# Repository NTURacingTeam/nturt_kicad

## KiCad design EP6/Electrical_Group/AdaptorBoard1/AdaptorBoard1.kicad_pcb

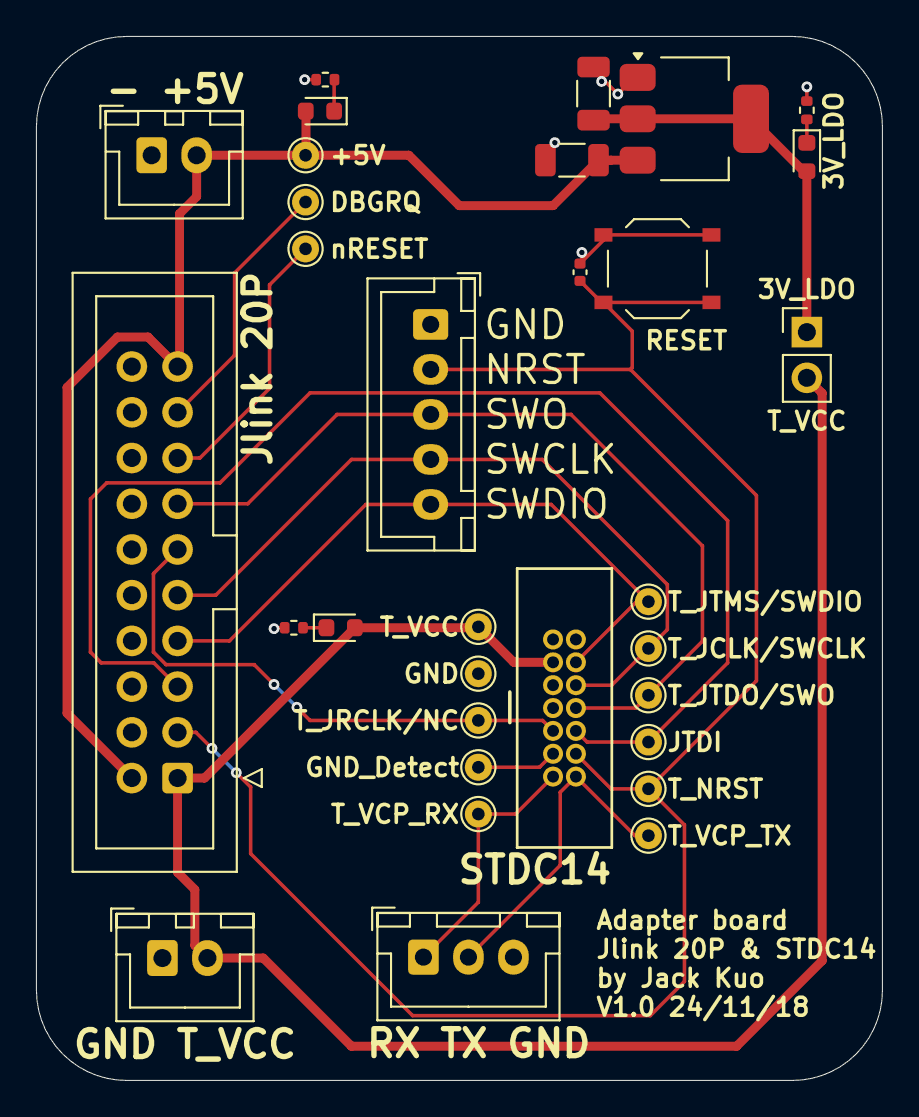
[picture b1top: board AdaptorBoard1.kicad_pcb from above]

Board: 2 copper layers, 47.0 x 58.0 mm, 32 parts (0 on the bottom side), 18 nets.

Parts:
C1, C2: 47u 10V; C_1206_3216Metric
C3: 0u1; C_0402_1005Metric
D1: RED 3V3; LED_0603_1608Metric
D2: RED 5V; LED_0603_1608Metric
D3: RED T_VCC; LED_0603_1608Metric
J1: Jlink20p; IDC-Header_2x10_P2.54mm_Vertical
J2: SWD; JST_XH_B5B-XH-A_1x05_P2.50mm_Vertical
J11: T_VCC; JST_XH_B2B-XH-A_1x02_P2.50mm_Vertical
J12: VCP_UART; JST_XH_B3B-XH-A_1x03_P2.50mm_Vertical
J13: 5V; JST_XH_B2B-XH-A_1x02_P2.50mm_Vertical
J17: STDIC 14p; box_header_14P_pitch127
JP1: 3.3V T_VCC; PinHeader_1x02_P2.54mm_Vertical
R1, R2, R3: 1k; R_0402_1005Metric
SW1: TS-1187A-B-A-B; SW_Push_1P1T_XKB_TS-1187A
TP1, TP2: T_VCC; TestPoint_THTPad_D1.5mm_Drill0.7mm
TP3: T_JRCLK/NC; TestPoint_THTPad_D1.5mm_Drill0.7mm
TP4: GND_DETECT; TestPoint_THTPad_D1.5mm_Drill0.7mm
TP5: T_VCP_RX; TestPoint_THTPad_D1.5mm_Drill0.7mm
TP8: T_JTMS/SWDIO; TestPoint_THTPad_D1.5mm_Drill0.7mm
TP9: T_JCLK/SWCLK; TestPoint_THTPad_D1.5mm_Drill0.7mm
TP10: T_JTDO/SWO; TestPoint_THTPad_D1.5mm_Drill0.7mm
TP11: T_NRST; TestPoint_THTPad_D1.5mm_Drill0.7mm
TP12: T_JTDI/NC; TestPoint_THTPad_D1.5mm_Drill0.7mm
TP13: T_VCP_TX; TestPoint_THTPad_D1.5mm_Drill0.7mm
TP14: nRESET; TestPoint_THTPad_D1.5mm_Drill0.7mm
TP15: DBGRQ; TestPoint_THTPad_D1.5mm_Drill0.7mm
TP16: +5V; TestPoint_THTPad_D1.5mm_Drill0.7mm
U1: AMS1117-3.3; SOT-223-3_TabPin2

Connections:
/STDIC14_JLINK20p/3V_LDO: C2.1, D1.2 (A), JP1.1 (A), U1.2 (VO)
/STDIC14_JLINK20p/+5V: C1.1, D2.2 (A), J1.2, J1.19, J13.2, TP16.1, U1.3 (VI)
/STDIC14_JLINK20p/DBGRQ: J1.17, TP15.1
/STDIC14_JLINK20p/GND_Detect: J17.11 (GNDDetect), TP4.1
/STDIC14_JLINK20p/T_JCLK/SWCLK: J1.9, J2.4, J17.6 (JCLK/SWCLK), TP9.1
/STDIC14_JLINK20p/T_JRCLK/NC: J1.11, J17.9 (JRCLK/NC), TP3.1
/STDIC14_JLINK20p/T_JTDI/NC: J1.5, J17.10 (JTDI/NC), TP12.1
/STDIC14_JLINK20p/T_JTDO/SWO: J1.13, J2.3, J17.8 (JTDO/SWO), TP10.1
/STDIC14_JLINK20p/T_JTMS/SWDIO: J1.7, J2.5, J17.4 (JTMS/SWDIO), TP8.1
/STDIC14_JLINK20p/T_NRST: C3.1, J1.3, J2.2, J17.12 (~RST), SW1.2, TP11.1
/STDIC14_JLINK20p/T_VCC: D3.2 (A), J1.1, J11.2, J17.3 (VCC), JP1.2 (B), TP1.1
/STDIC14_JLINK20p/T_VCP_RX: J12.1, J17.13 (VCP_RX), TP5.1
/STDIC14_JLINK20p/T_VCP_TX: J12.2, J17.14 (VCP_TX), TP13.1
/STDIC14_JLINK20p/nRESET: J1.15, TP14.1
GND: C1.2, C2.2, C3.2, J1.4, J1.6, J1.8, J1.10, J1.12, J1.14, J1.16, J1.18, J1.20, J2.1, J11.1, J12.3, J13.1, J17.5 (GND), J17.7 (GND), R1.2, R2.2, R3.2, SW1.1, TP2.1, U1.1 (GND)
unnamed: D1.1 (K), R1.1
unnamed: D2.1 (K), R2.1
unnamed: D3.1 (K), R3.1

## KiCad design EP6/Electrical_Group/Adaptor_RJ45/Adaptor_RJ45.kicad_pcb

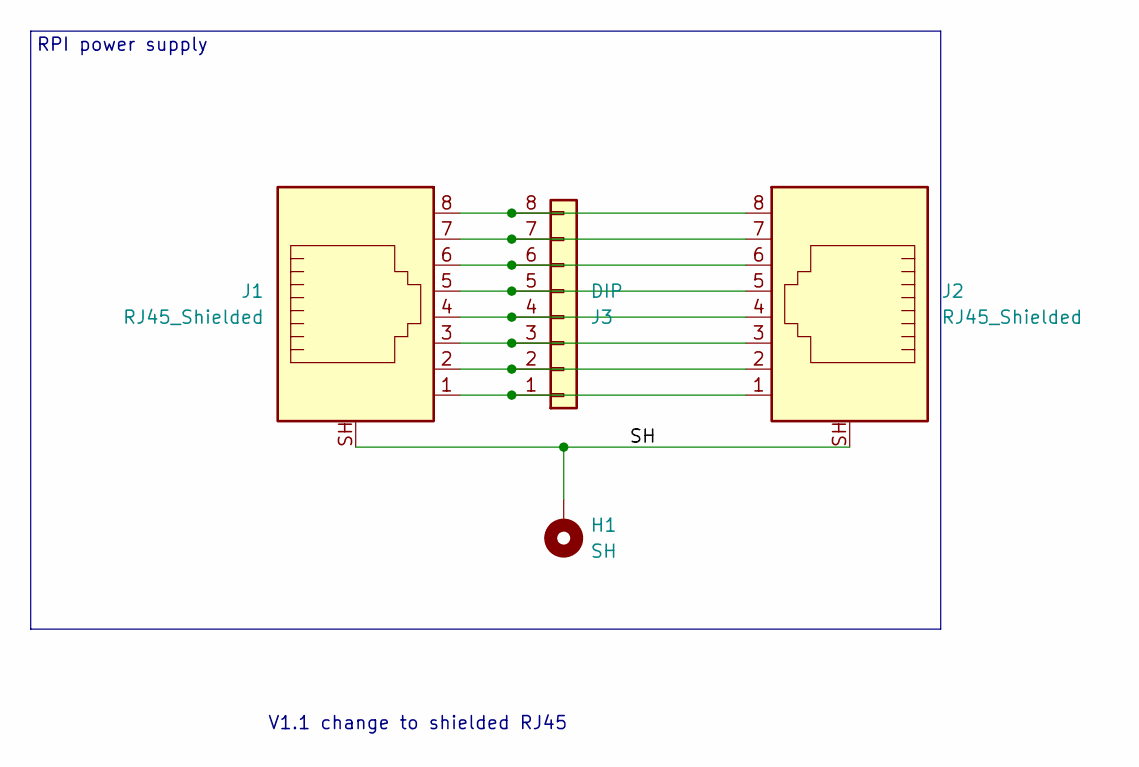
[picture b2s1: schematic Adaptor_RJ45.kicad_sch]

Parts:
H1: SH; MountingHole_3.2mm_M3_Pad
J1, J2: RJ45_Shielded; RJ45_Ninigi_GE
J3: DIP; PinHeader_2x04_P2.54mm_Vertical

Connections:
/SH: H1.1, J1.SH, J2.SH
unnamed: J1.1, J2.1, J3.1
unnamed: J1.2, J2.2, J3.2
unnamed: J1.3, J2.3, J3.3
unnamed: J1.4, J2.4, J3.4
unnamed: J1.5, J2.5, J3.5
unnamed: J1.6, J2.6, J3.6
unnamed: J1.7, J2.7, J3.7
unnamed: J1.8, J2.8, J3.8

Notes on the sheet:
RPI power supply
V1.1 change to shielded RJ45

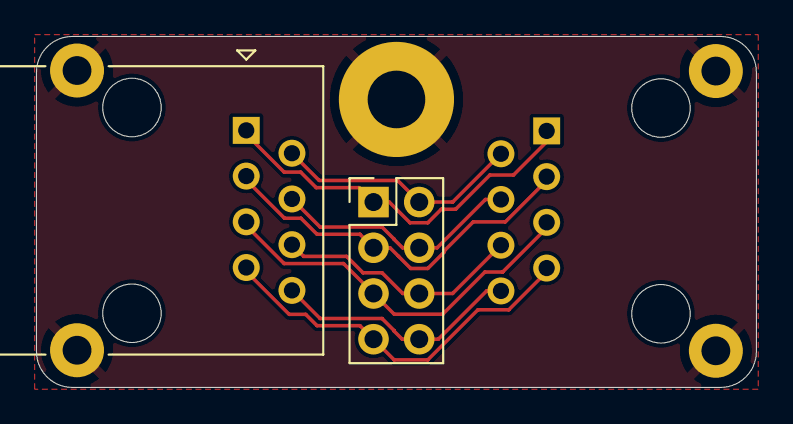
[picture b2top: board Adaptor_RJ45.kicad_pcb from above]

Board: 2 copper layers, 40.0 x 19.5 mm, 4 parts (1 on the bottom side), 9 nets.

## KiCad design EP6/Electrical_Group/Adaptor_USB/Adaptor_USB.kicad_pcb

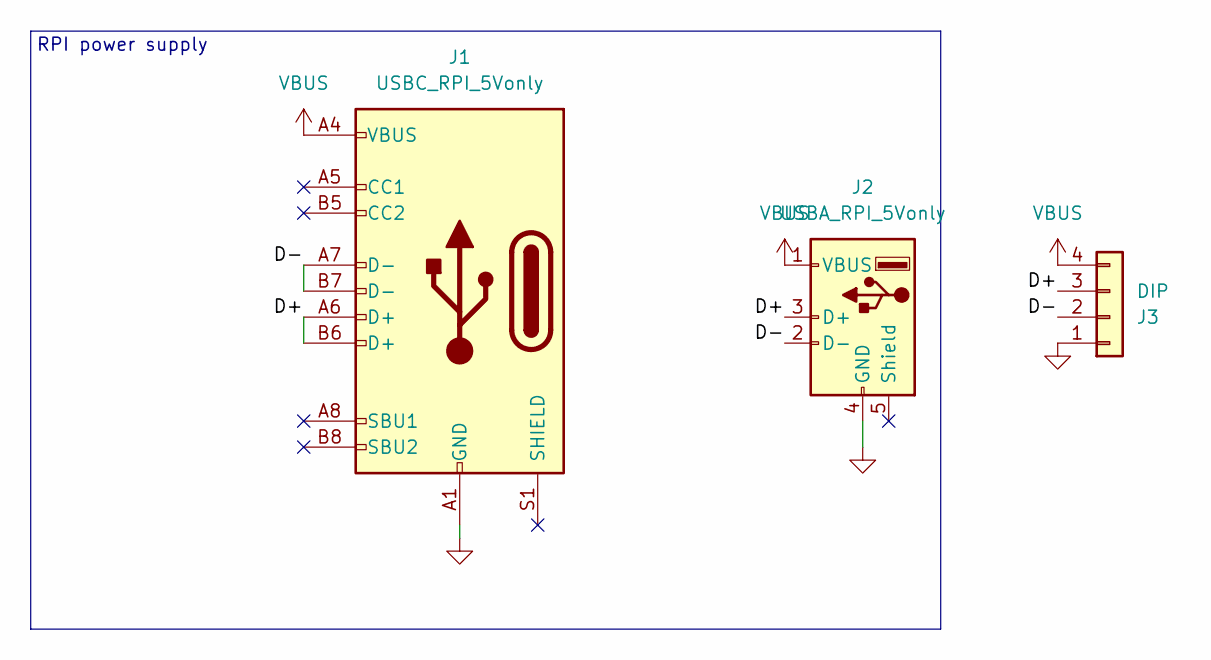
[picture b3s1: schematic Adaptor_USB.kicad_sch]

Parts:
J1: USBC_RPI_5Vonly; USB_C_Receptacle_GCT_USB4105-xx-A_16P_TopMnt_Horizontal
J2: USBA_RPI_5Vonly; USB_A_Molex_67643_Horizontal
J3: DIP; PinHeader_1x04_P2.54mm_Vertical; Part Number 1-0401FBV0T

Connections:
/D+: J1.A6 (D+), J1.B6 (D+), J2.3 (D+), J3.3
/D-: J1.A7 (D-), J1.B7 (D-), J2.2 (D-), J3.2
GND: J1.A1 (GND), J1.A12 (GND), J1.B1 (GND), J1.B12 (GND), J2.4 (GND), J3.1
VBUS: J1.A4 (VBUS), J1.A9 (VBUS), J1.B4 (VBUS), J1.B9 (VBUS), J2.1 (VBUS), J3.4

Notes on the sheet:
RPI power supply

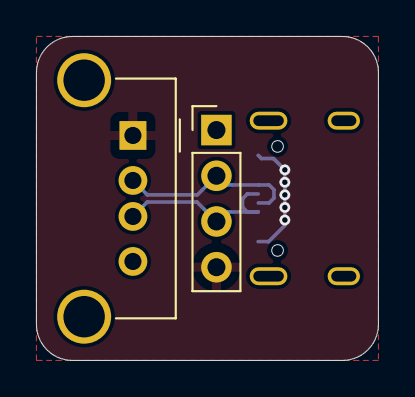
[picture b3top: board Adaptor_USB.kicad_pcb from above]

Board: 2 copper layers, 19.0 x 18.0 mm, 3 parts (1 on the bottom side), 4 nets.

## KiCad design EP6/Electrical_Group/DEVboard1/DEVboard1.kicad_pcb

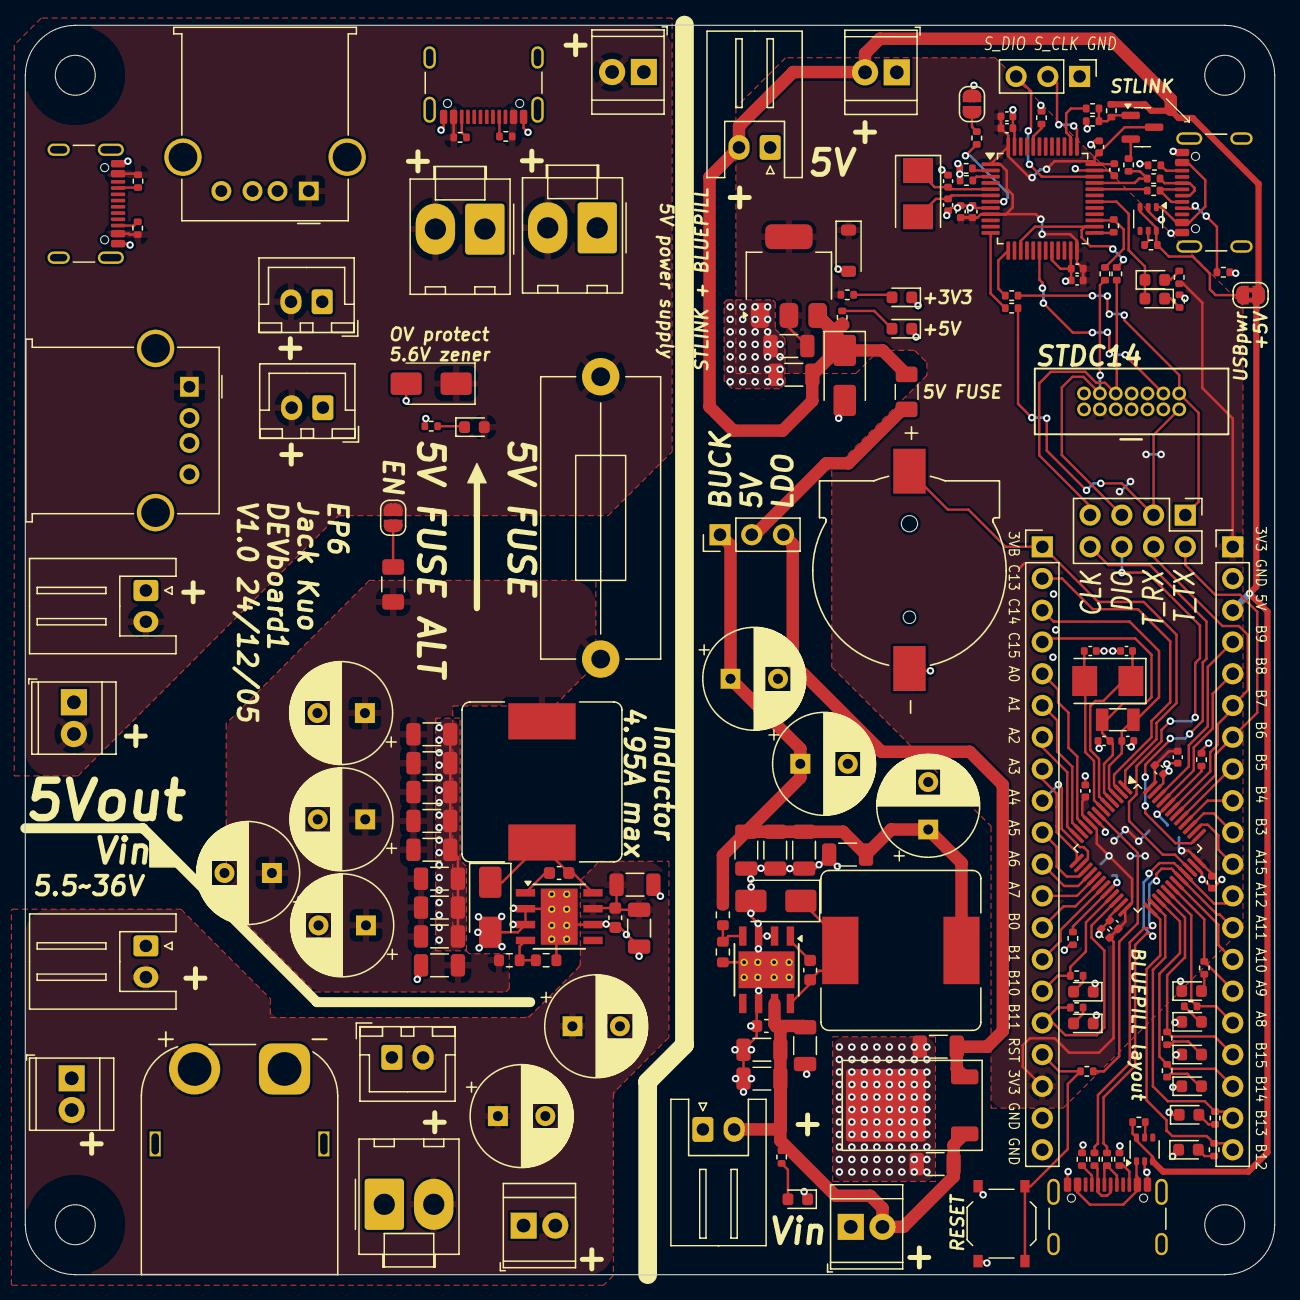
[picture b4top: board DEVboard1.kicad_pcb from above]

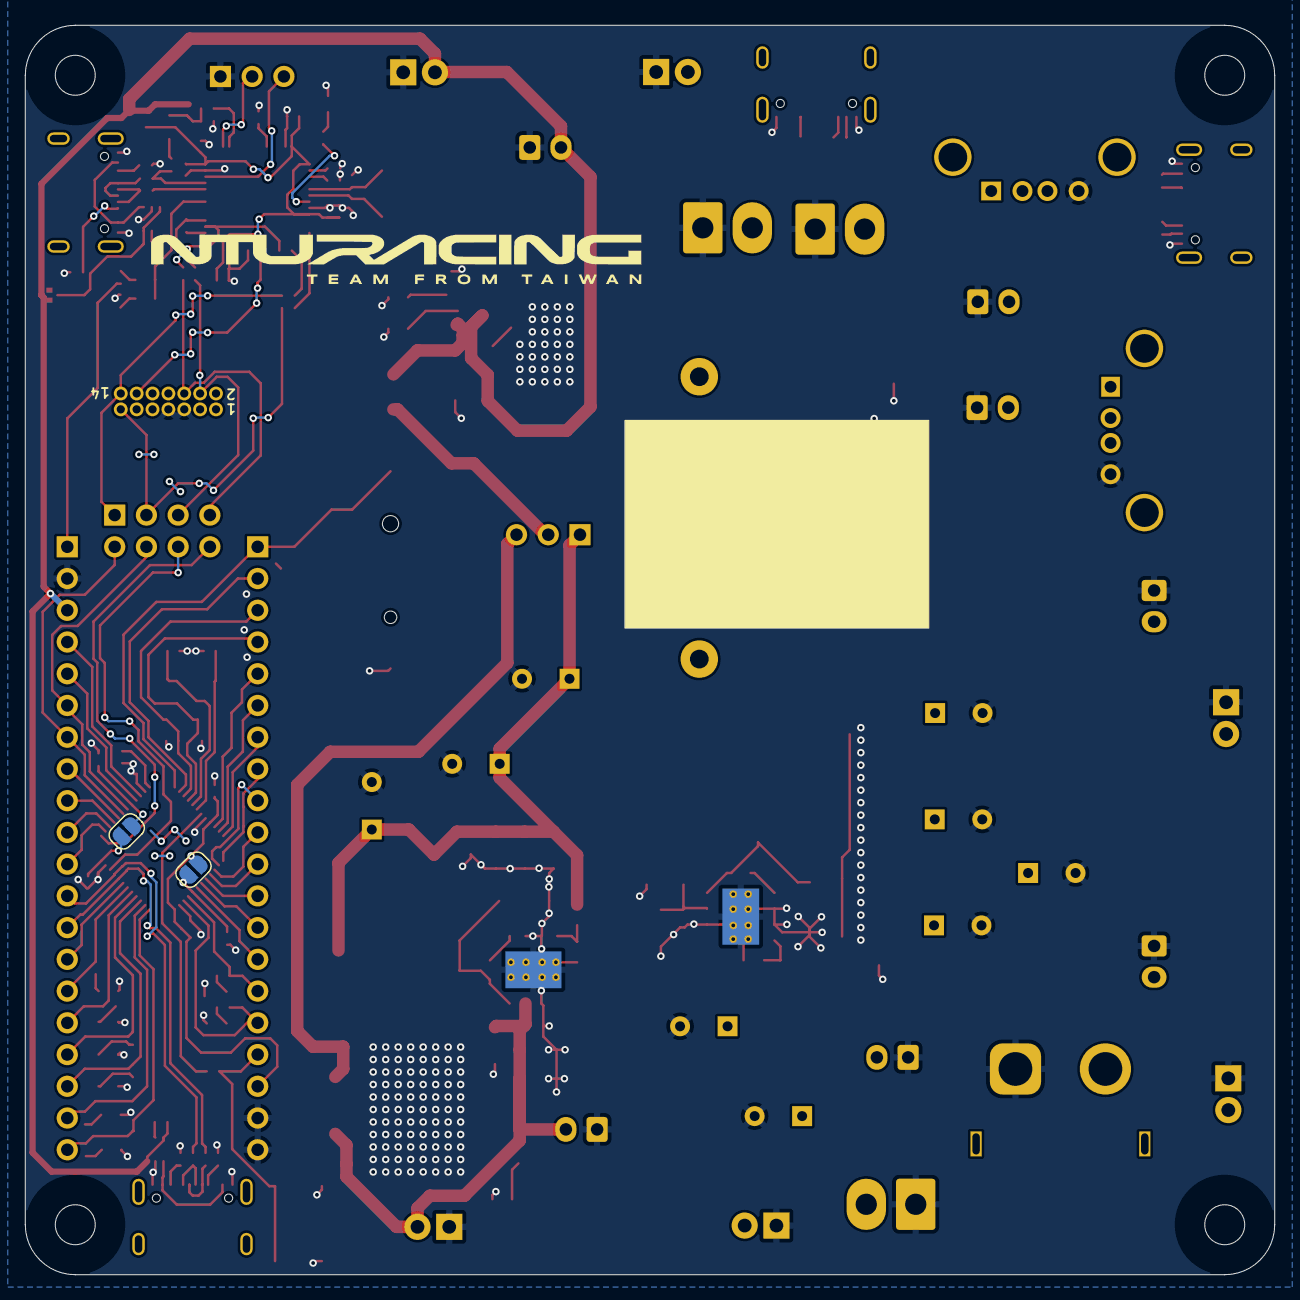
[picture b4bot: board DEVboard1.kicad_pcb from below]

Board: 2 copper layers, 100.0 x 100.0 mm, 179 parts (2 on the bottom side), 114 nets.

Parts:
BT1: 1056; BAT_1056
C1, C2, C3, C4, C13, C14: 10u 6V; C_0402_1005Metric
C5, C6, C7, C8, C15, C16, C17, C18: 0u1; C_0402_1005Metric
C9, C10: 33p; C_0402_1005Metric
C11, C12: 15p; C_0402_1005Metric
C19, C20: 30p; C_0402_1005Metric
C21, C22: 47u 10V; C_1206_3216Metric
C23, C33: 10n; C_0603_1608Metric
C24, C25, C31, C32, C34, C35, C45: 10u 35V; C_1206_3216Metric
C26, C37: 0u1; C_0603_1608Metric
C27, C28, C29, C30, C38, C39, C40, C41, C42, C46, C47, C48, C49: 22u 25V; C_1206_3216Metric
C36, C43, C44, C50, C51, C52, C53, C54, C55: 330u 25V; CP_Radial_D8.0mm_P3.80mm
D1: YELLOW led; LED_0603_1608Metric
D2: 3.3V 123 (BZT52B3V3); D_SOD-123
D3, D17, D19, D20: RED LED; LED_0603_1608Metric
D4: RED led; LED_0603_1608Metric
D5, D18: 5.6V 1SMA5919A; D_SMA
D6, D7, D9, D10, D11, D12, D13, D14: WHITE LED; LED_0603_1608Metric
D8, D15: SS54; D_SMA
F1: 0.5A; Fuse_1206_3216Metric
F2: 5Vbuck_fuse; Fuseholder_Cylinder-5x20mm_Stelvio-Kontek_PTF78_Horizontal_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
F3: 5Vbuck_PPTC; Fuse_1206_3216Metric
H1, H2, H3, H4: MountingHole; MountingHole_3.2mm_M3
J1, J4: USB_C_stm32; USB_C_Receptacle_GCT_USB4105-xx-A_16P_TopMnt_Horizontal
J2, J3: Conn_01x20; PinHeader_1x20_P2.54mm_Vertical
J5: STDC14; box_header_14P_pitch127
J6: DEBUG; PinHeader_2x04_P2.54mm_Vertical
J7: S_SWD; PinHeader_1x03_P2.54mm_Vertical
J8: 5V_source; PinHeader_1x03_P2.54mm_Vertical
J9, J11, J29: +5V; JST_XH_S2B-XH-A_1x02_P2.50mm_Horizontal
J10: +5V; TerminalBlock_TE_282834-2_1x02_P2.54mm_Horizontal
J12, J27: Vin; TerminalBlock_TE_282834-2_1x02_P2.54mm_Horizontal
J13: Vin; Molex_KK-396_A-41791-0002_1x02_P3.96mm_Vertical
J14: Vin; JST_XH_B2B-XH-A_1x02_P2.50mm_Vertical
J15: Vin; AMASS_XT60PW-M_1x02_P7.20mm_Horizontal
J16, J25, J26: +24V; TerminalBlock_TE_282834-2_1x02_P2.54mm_Horizontal
J17, J18: +5V; Molex_KK-396_A-41791-0002_1x02_P3.96mm_Vertical
J19, J22: USBC_RPI_5Vonly; USB_C_Receptacle_GCT_USB4105-xx-A_16P_TopMnt_Horizontal
J20, J23: USBA_RPI_5Vonly; USB_A_Molex_67643_Horizontal
J21, J24: +5V; JST_XH_B2B-XH-A_1x02_P2.50mm_Vertical
J30: Vin; JST_XH_S2B-XH-A_1x02_P2.50mm_Horizontal
JP1: BOOT0; SolderJumper-2_P1.3mm_Open_RoundedPad1.0x1.5mm
JP2: BOOT1; SolderJumper-2_P1.3mm_Open_RoundedPad1.0x1.5mm
JP3: S_RESET; SolderJumper-2_P1.3mm_Open_RoundedPad1.0x1.5mm
JP4: VBUS_5V; SolderJumper-2_P1.3mm_Bridged2Bar_RoundedPad1.0x1.5mm
JP5: PPTC_EN; SolderJumper-2_P1.3mm_Open_RoundedPad1.0x1.5mm
L1, L2: 22uH 3.7A (SMDRI129-220MT); L_Bourns_SRR1260
Q1: MMBT3904; SOT-23
R1, R4, R7, R8, R19, R21, R27, R28: 100R; R_0402_1005Metric
R2, R5, R10: 100k; R_0402_1005Metric
R3, R6, R11, R13, R18, R20, R26: 10k; R_0402_1005Metric
R9, R15: 220R; R_0402_1005Metric
R12, R14: 10R; R_0402_1005Metric
R16, R17, R23, R24: 5k1; R_0402_1005Metric
R22: 33k; R_0402_1005Metric
R25: 1k5; R_0402_1005Metric
R31, R32, R33, R35, R36, R37, R38, R39, R40, R43, R46, R48: 1k; R_0402_1005Metric
R34, R41: 47k 1%; R_0603_1608Metric
R42, R44: 15k 1%; R_0603_1608Metric
R45, R47, R49, R50: 56k; R_0402_1005Metric
SW1: TS-1187A-B-A-B; SW_Push_1P1T_XKB_TS-1187A
U1, U2: STM32F103CBT6; LQFP-48_7x7mm_P0.5mm
U3, U5: LM66100DCK; SOT-363_SC-70-6
U4: AMS1117-3.3; SOT-223-3_TabPin2
U6: L78M05ABDT; TO-252-2
U7, U8: TPS5430DDAR; TI_SO-PowerPAD-8_ThermalVias
Y1, Y3: 8MHz X50328MSB2GI; Crystal_SMD_5032-2Pin_5.0x3.2mm
Y2: 32.768kHz Q13FC13500004; Crystal_SMD_3215-2Pin_3.2x1.5mm

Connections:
+3V3: C1.1, C2.1, C3.1, C4.1, C5.1, C6.1, C7.1, C8.1, C13.1, C14.1, C15.1, C16.1, C17.1, C18.1, C22.1, D2.1 (K), J2.18, J3.1, J5.3, JP1.2 (B), JP2.2 (B), Q1.3 (C), R9.1, R46.1, U1.9 (VDDA), U1.24 (VDD), U1.36 (VDD), U1.48 (VDD), U2.1 (VBAT), U2.9 (VDDA), U2.24 (VDD), U2.36 (VDD), U2.48 (VDD), U4.2 (VO)
+5V: C21.1, D5.1 (K), F1.2, J3.3, J11.2, J26.2, JP4.2 (B), R20.1, R26.1, R48.1, U4.3 (VI), U5.3 (~CE), U5.6 (VOUT)
/5V_buck_FB: R34.2, R42.1, U7.4 (VSENSE)
/5V_buck_sw: C23.2, D8.1 (K), L1.1, U7.8 (PH)
/+5V_LDO: C32.2, J8.3, U6.3 (OUT)
/+5V_buck: C27.1, C28.1, C29.1, C30.1, C36.1, C54.1, C55.1, J8.1, L1.2, R34.1
/MCU/3VB: BT1.P, J2.1, U1.1 (VBAT)
/MCU/BOOT0: JP1.1 (A), R5.1, U1.44 (BOOT0)
/MCU/BOOT1: JP2.1 (A), R2.1, U1.20 (PB2)
/MCU/NRST: R3.2, U1.7 (NRST)
/MCU/OSC32_IN: C11.1, J2.3, U1.3 (PC14), Y2.1
/MCU/OSC32_OUT: C12.1, J2.4, U1.4 (PC15), Y2.2
/MCU/OSC_IN: C9.1, U1.5 (PD0), Y1.1
/MCU/OSC_OUT: C10.1, U1.6 (PD1), Y1.2
/MCU/PA0: J2.5, U1.10 (PA0)
/MCU/PA1: J2.6, U1.11 (PA1)
/MCU/PA2: J2.7, U1.12 (PA2)
/MCU/PA3: J2.8, U1.13 (PA3)
/MCU/PA4: J2.9, U1.14 (PA4)
/MCU/PA5: J2.10, U1.15 (PA5)
/MCU/PA6: J2.11, U1.16 (PA6)
/MCU/PA7: J2.12, U1.17 (PA7)
/MCU/PA8: J3.16, R36.1, U1.29 (PA8)
/MCU/PA9: J3.15, R35.1, U1.30 (PA9)
/MCU/PA10: J3.14, U1.31 (PA10)
/MCU/PA13: J6.6, U1.34 (PA13)
/MCU/PA14: J6.8, U1.37 (PA14)
/MCU/PA15: J3.11, U1.38 (PA15)
/MCU/PB0: J2.13, U1.18 (PB0)
/MCU/PB1: J2.14, U1.19 (PB1)
/MCU/PB3: J3.10, U1.39 (PB3)
/MCU/PB4: J3.9, U1.40 (PB4)
/MCU/PB5: J3.8, U1.41 (PB5)
/MCU/PB6: J3.7, J6.2, U1.42 (PB6)
/MCU/PB7: J3.6, J6.4, U1.43 (PB7)
/MCU/PB8: J3.5, U1.45 (PB8)
/MCU/PB9: J3.4, U1.46 (PB9)
/MCU/PB10: J2.15, R32.1, U1.21 (PB10)
/MCU/PB11: J2.16, R33.1, U1.22 (PB11)
/MCU/PB12: J3.20, R40.1, U1.25 (PB12)
/MCU/PB13: J3.19, R39.1, U1.26 (PB13)
/MCU/PB14: J3.18, R38.1, U1.27 (PB14)
/MCU/PB15: J3.17, R37.1, U1.28 (PB15)
/MCU/PC13: J2.2, U1.2 (PC13)
/MCU/RESET: J2.17, R3.1, SW1.2
/MCU/USB_D+: J1.A6 (D+), J1.B6 (D+), R14.2
/MCU/USB_D-: J1.A7 (D-), J1.B7 (D-), R12.2
/MCU/USB_DN: J3.13, R12.1, U1.32 (PA11)
/MCU/USB_DP: J3.12, R14.1, U1.33 (PA12)
/MCU/VBUS: J1.A4 (VBUS), J1.A9 (VBUS), J1.B4 (VBUS), J1.B9 (VBUS), U5.1 (VIN)
/STlink/BOOT0: R10.1, U2.44 (BOOT0)
/STlink/LED_STLINK: D1.1 (K), D4.2 (A), U2.30 (PA9)
/STlink/OSC_IN: C19.1, U2.5 (PD0), Y3.1
/STlink/OSC_OUT: C20.1, U2.6 (PD1), Y3.2
/STlink/RENUM: R21.1, U2.38 (PA15)
/STlink/S_CLK: J7.2, U2.37 (PA14)
/STlink/S_DIO: J7.3, U2.34 (PA13)
/STlink/S_NRST: R6.2, U2.7 (NRST)
/STlink/USART2_RX: R4.1, U2.13 (PA3)
/STlink/USART2_TX: R1.1, U2.12 (PA2)
/STlink/USB_D+: J4.A6 (D+), J4.B6 (D+), R28.1
/STlink/USB_D-: J4.A7 (D-), J4.B7 (D-), R27.1
/STlink/USB_DN: R27.2, U2.32 (PA11)
/STlink/USB_DP: R25.2, R28.2, U2.33 (PA12)
/STlink/VBUS: J4.A4 (VBUS), J4.A9 (VBUS), J4.B4 (VBUS), J4.B9 (VBUS), U3.1 (VIN)
/STlink/t_CLK: R7.1, U2.15 (PA5), U2.26 (PB13)
/STlink/t_DIO: R8.1, R19.1, U2.27 (PB14)
/T_NRST: J5.12, U2.18 (PB0)
/T_SWCLK: J5.6, J6.7, R7.2
/T_SWDIO: J5.4, J6.5, R8.2
/T_VCP_RX: J5.13, J6.3, R1.2
/T_VCP_TX: J5.14, J6.1, R4.2
/extPWR/5V_buck_FB: R41.2, R44.1, U8.4 (VSENSE)
/extPWR/5V_buck_sw: C33.2, D15.1 (K), L2.1, U8.8 (PH)
/extPWR/+5V_buck: D17.2 (A), D18.1 (K), F2.2, J10.2, J17.2, J18.2, J19.A4 (VBUS), J19.A9 (VBUS), J19.B4 (VBUS), J19.B9 (VBUS), J20.1 (VBUS), J21.2, J22.A4 (VBUS), J22.A9 (VBUS), J22.B4 (VBUS), J22.B9 (VBUS), J23.1 (VBUS), J24.2, J25.2, J29.2, JP5.2 (B), R45.1, R47.1, R49.1, R50.1
/extPWR/+5V_buck_raw: C38.1, C39.1, C40.1, C41.1, C42.1, C43.1, C44.1, C46.1, C47.1, C48.1, C49.1, C50.1, C51.1, F2.1, F3.1, L2.2, R41.1
/extPWR/Vin: C34.1, C35.1, C37.2, C52.1, C53.1, J12.2, J13.2, J14.2, J15.2, J27.2, J30.2, U8.7 (VIN)
GND: BT1.N, C1.2, C2.2, C3.2, C4.2, C5.2, C6.2, C7.2, C8.2, C9.2, C10.2, C11.2, C12.2, C13.2, C14.2, C15.2, C16.2, C17.2, C18.2, C19.2, C20.2, C21.2, C22.2, C24.2, C25.2, C26.1, C27.2, C28.2, C29.2, C30.2, C31.2, C32.1, C34.2, C35.2, C36.2, C37.1, C38.2, C39.2, C40.2, C41.2, C42.2, C43.2, C44.2, C45.2, C46.2, C47.2, C48.2, C49.2, C50.2, C51.2, C52.2, C53.2, C54.2, C55.2, D2.2 (A), D3.1 (K), D5.2 (A), D6.1 (K), D7.1 (K), D8.2 (A), D9.1 (K), D10.1 (K), D11.1 (K), D12.1 (K), D13.1 (K), D14.1 (K), D15.2 (A), D18.2 (A), D19.1 (K), D20.1 (K), J1.A1 (GND), J1.A12 (GND), J1.B1 (GND), J1.B12 (GND), J2.19, J2.20, J3.2, J4.A1 (GND), J4.A12 (GND), J4.B1 (GND), J4.B12 (GND), J5.5, J5.7, J7.1, J9.1, J10.1, J11.1, J12.1, J13.1, J14.1, J15.1, J16.1, J17.1, J18.1, J19.A1 (GND), J19.A12 (GND), J19.B1 (GND), J19.B12 (GND), J20.4 (GND), J21.1, J22.A1 (GND), J22.A12 (GND), J22.B1 (GND), J22.B12 (GND), J23.4 (GND), J24.1, J25.1, J26.1, J27.1, J29.1, J30.1, JP3.1 (A), R2.2, R5.2, R10.2, R11.2, R13.2, R15.2, R16.1, R17.1, R22.2, R23.1, R24.1, R42.2, R43.2, R44.2, SW1.1, U1.8 (VSSA), U1.23 (VSS), U1.35 (VSS), U1.47 (VSS), U2.8 (VSSA), U2.20 (PB2), U2.23 (VSS), U2.35 (VSS), U2.47 (VSS), U3.2 (GND), U4.1 (GND), U5.2 (GND), U6.2, U7.2 (NC), U7.3 (NC), U7.6 (GND), U7.9 (GNDPAD), U8.2 (NC), U8.3 (NC), U8.6 (GND), U8.9 (GNDPAD)
unnamed: D1.2 (A), R9.2
unnamed: D3.2 (A), R31.2
unnamed: D4.1 (K), R15.1
unnamed: D6.2 (A), R32.2
unnamed: D7.2 (A), R33.2
unnamed: D9.2 (A), R35.2
unnamed: D10.2 (A), R36.2
unnamed: D11.2 (A), R37.2
unnamed: D12.2 (A), R38.2
unnamed: D13.2 (A), R39.2
unnamed: D14.2 (A), R40.2
unnamed: D17.1 (K), R43.1
unnamed: D19.2 (A), R48.2
unnamed: D20.2 (A), R46.2
unnamed: J1.A5 (CC1), R16.2
unnamed: J1.B5 (CC2), R17.2
unnamed: J4.A5 (CC1), R23.2
unnamed: J4.B5 (CC2), R24.2
unnamed: F1.1, J8.2
unnamed: J19.A5 (CC1), R45.2
unnamed: J19.B5 (CC2), R47.2
unnamed: J22.A5 (CC1), R49.2
unnamed: J22.B5 (CC2), R50.2
unnamed: JP3.2 (B), R6.1
unnamed: JP4.1 (A), R18.1, U3.3 (~CE), U3.6 (VOUT)
unnamed: F3.2, JP5.1 (A)
unnamed: Q1.1 (B), R20.2, R21.2, R22.1
unnamed: Q1.2 (E), R25.1
unnamed: R19.2, U2.25 (PB12)
unnamed: R11.1, U2.2 (PC13)
unnamed: R13.1, U2.3 (PC14)
unnamed: R18.2, U3.5 (ST)
unnamed: R26.2, U5.5 (ST)
unnamed: C23.1, U7.1 (BOOT)
unnamed: C33.1, U8.1 (BOOT)
VBUS: C24.1, C25.1, C26.2, C31.1, C45.1, J9.2, J16.2, R31.1, U6.1 (IN), U7.7 (VIN)

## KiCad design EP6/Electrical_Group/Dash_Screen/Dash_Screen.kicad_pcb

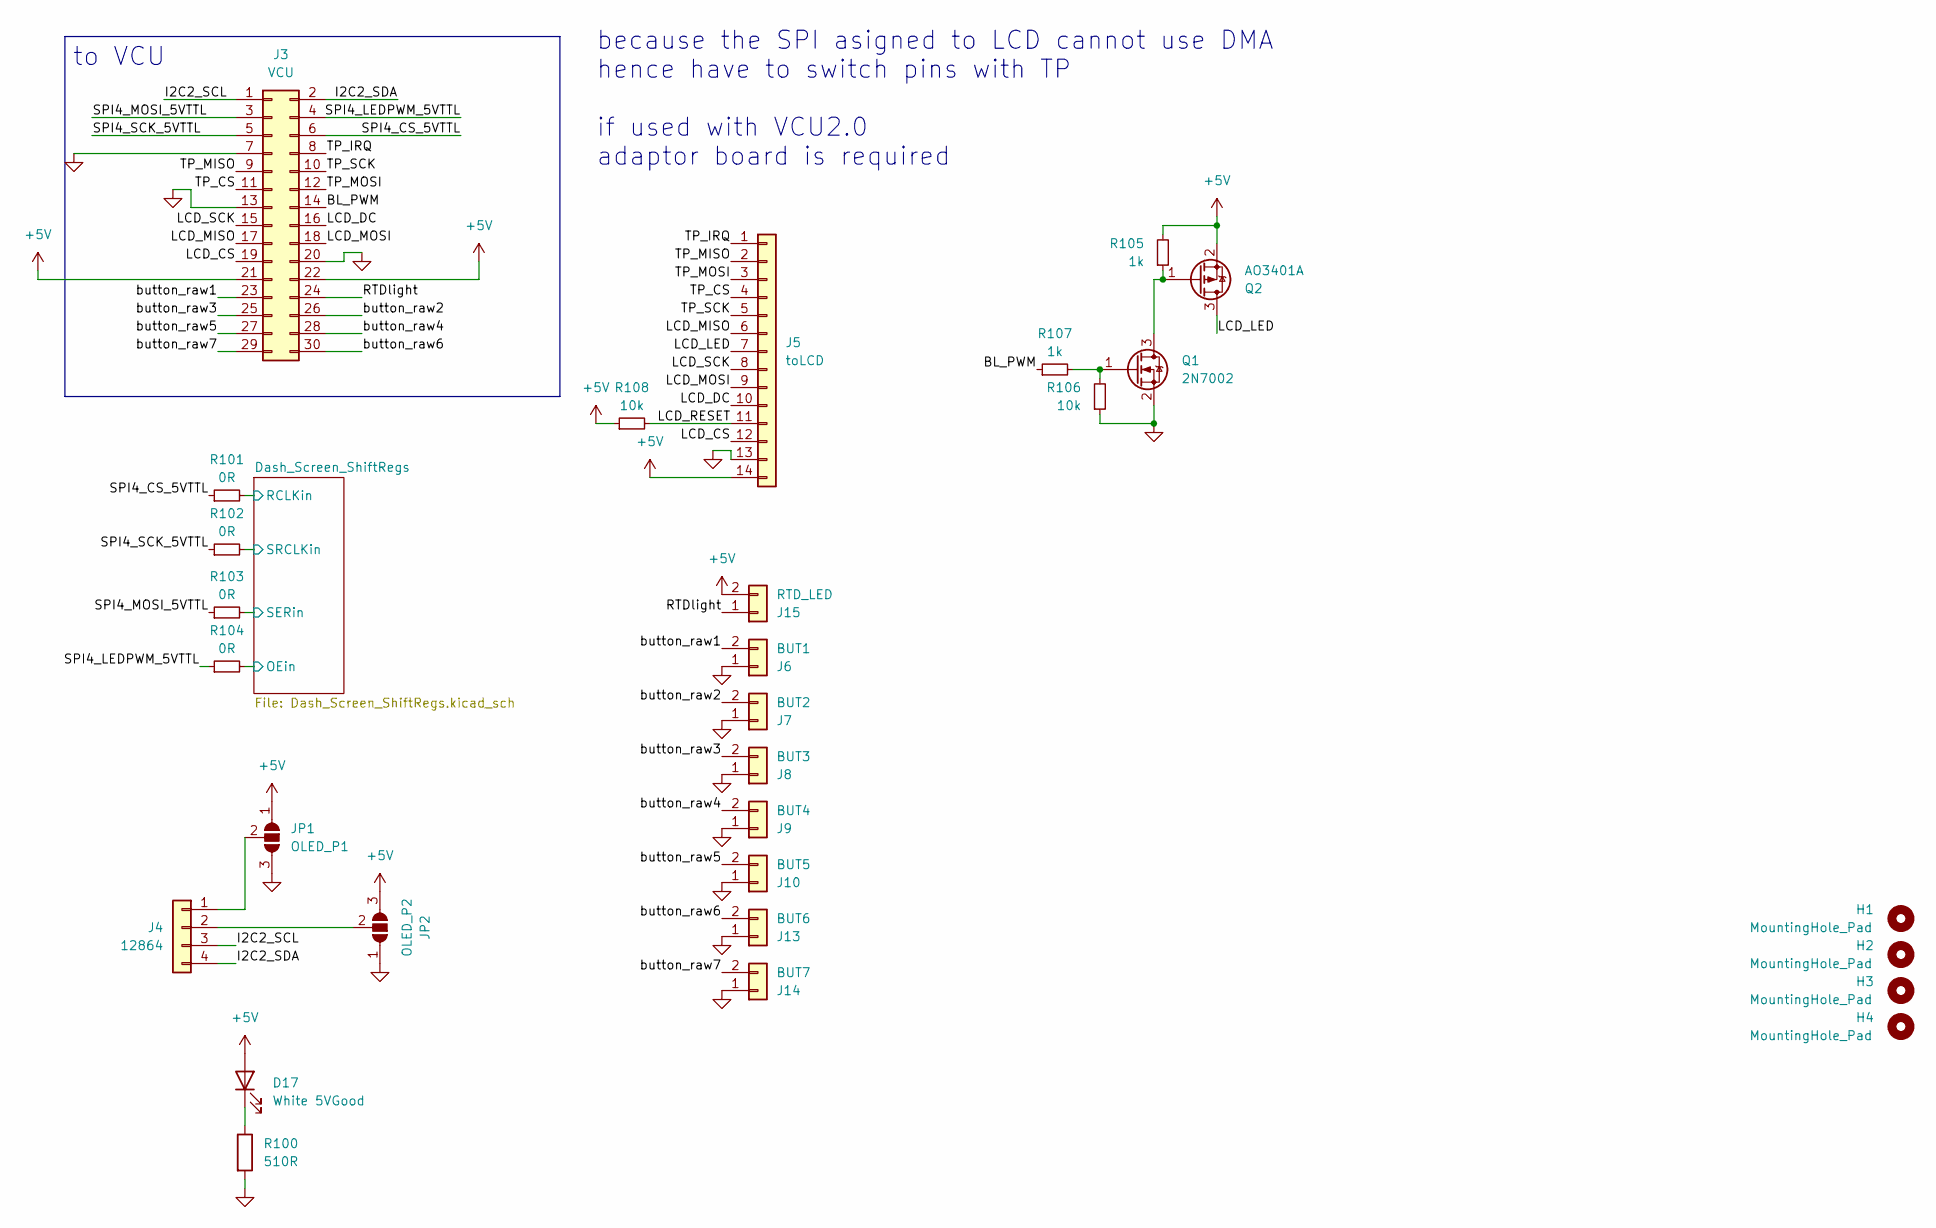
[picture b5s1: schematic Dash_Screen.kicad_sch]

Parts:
D17: White 5VGood; LED_0603_1608Metric
H1, H2, H3, H4: MountingHole_Pad; MountingHole_3.2mm_M3
J3: VCU; IDC-Header_2x15_P2.54mm_Vertical_SMD
J4: 12864; 12864_1.3_I2C
J5: toLCD; PinHeader_1x14_P2.54mm_Horizontal
J6: BUT1; JST_PH_S2B-PH-K_1x02_P2.00mm_Horizontal
J7: BUT2; JST_PH_S2B-PH-K_1x02_P2.00mm_Horizontal
J8: BUT3; JST_PH_S2B-PH-K_1x02_P2.00mm_Horizontal
J9: BUT4; JST_PH_S2B-PH-K_1x02_P2.00mm_Horizontal
J10: BUT5; JST_PH_S2B-PH-K_1x02_P2.00mm_Horizontal
J13: BUT6; JST_PH_S2B-PH-K_1x02_P2.00mm_Horizontal
J14: BUT7; JST_PH_S2B-PH-K_1x02_P2.00mm_Horizontal
J15: RTD_LED; JST_PH_S2B-PH-K_1x02_P2.00mm_Horizontal
JP1: OLED_P1; SolderJumper-3_P1.3mm_Open_RoundedPad1.0x1.5mm
JP2: OLED_P2; SolderJumper-3_P1.3mm_Open_RoundedPad1.0x1.5mm
Q1: 2N7002; SOT-23
Q2: AO3401A; SOT-23
R100: 510R; R_0603_1608Metric
R101, R102, R103, R104: 0R; R_0603_1608Metric
R105, R107: 1k; R_0603_1608Metric
R106, R108: 10k; R_0603_1608Metric

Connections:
+5V: D17.2 (A), J3.21, J3.22, J5.14, J15.2, JP1.1 (A), JP2.3 (B), Q2.2 (S), R105.2, R108.1; also elsewhere on the board
/BL_PWM: J3.14, R107.1
/Dash_Screen_ShiftRegs/OE: R104.2; also elsewhere on the board
/Dash_Screen_ShiftRegs/RCLK: R101.2; also elsewhere on the board
/Dash_Screen_ShiftRegs/SER: R103.2; also elsewhere on the board
/Dash_Screen_ShiftRegs/SRCLK: R102.2; also elsewhere on the board
/I2C2_SCL: J3.1, J4.3
/I2C2_SDA: J3.2, J4.4
/LCD_CS: J3.19, J5.12
/LCD_DC: J3.16, J5.10
/LCD_LED: J5.7, Q2.3 (D)
/LCD_MISO: J3.17, J5.6
/LCD_MOSI: J3.18, J5.9
/LCD_RESET: J5.11, R108.2
/LCD_SCK: J3.15, J5.8
/RTDlight: J3.24, J15.1
/SPI4_CS_5VTTL: J3.6, R101.1
/SPI4_LEDPWM_5VTTL: J3.4, R104.1
/SPI4_MOSI_5VTTL: J3.3, R103.1
/SPI4_SCK_5VTTL: J3.5, R102.1
/TP_CS: J3.11, J5.4
/TP_IRQ: J3.8, J5.1
/TP_MISO: J3.9, J5.2
/TP_MOSI: J3.12, J5.3
/TP_SCK: J3.10, J5.5
/button_raw1: J3.23, J6.2
/button_raw2: J3.26, J7.2
/button_raw3: J3.25, J8.2
/button_raw4: J3.28, J9.2
/button_raw5: J3.27, J10.2
/button_raw6: J3.30, J13.2
/button_raw7: J3.29, J14.2
GND: J3.7, J3.13, J3.20, J5.13, J6.1, J7.1, J8.1, J9.1, J10.1, J13.1, J14.1, JP1.3 (B), JP2.1 (A), Q1.2 (S), R100.2, R106.1; also elsewhere on the board
unnamed: D17.1 (K), R100.1
unnamed: J4.1, JP1.2 (C)
unnamed: J4.2, JP2.2 (C)
unnamed: Q1.3 (D), Q2.1 (G), R105.1
unnamed: Q1.1 (G), R106.2, R107.2

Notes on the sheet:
to VCU
because the SPI asigned to LCD cannot use DMA hence have to switch pins with TP if used with VCU2.0 adaptor board is required
